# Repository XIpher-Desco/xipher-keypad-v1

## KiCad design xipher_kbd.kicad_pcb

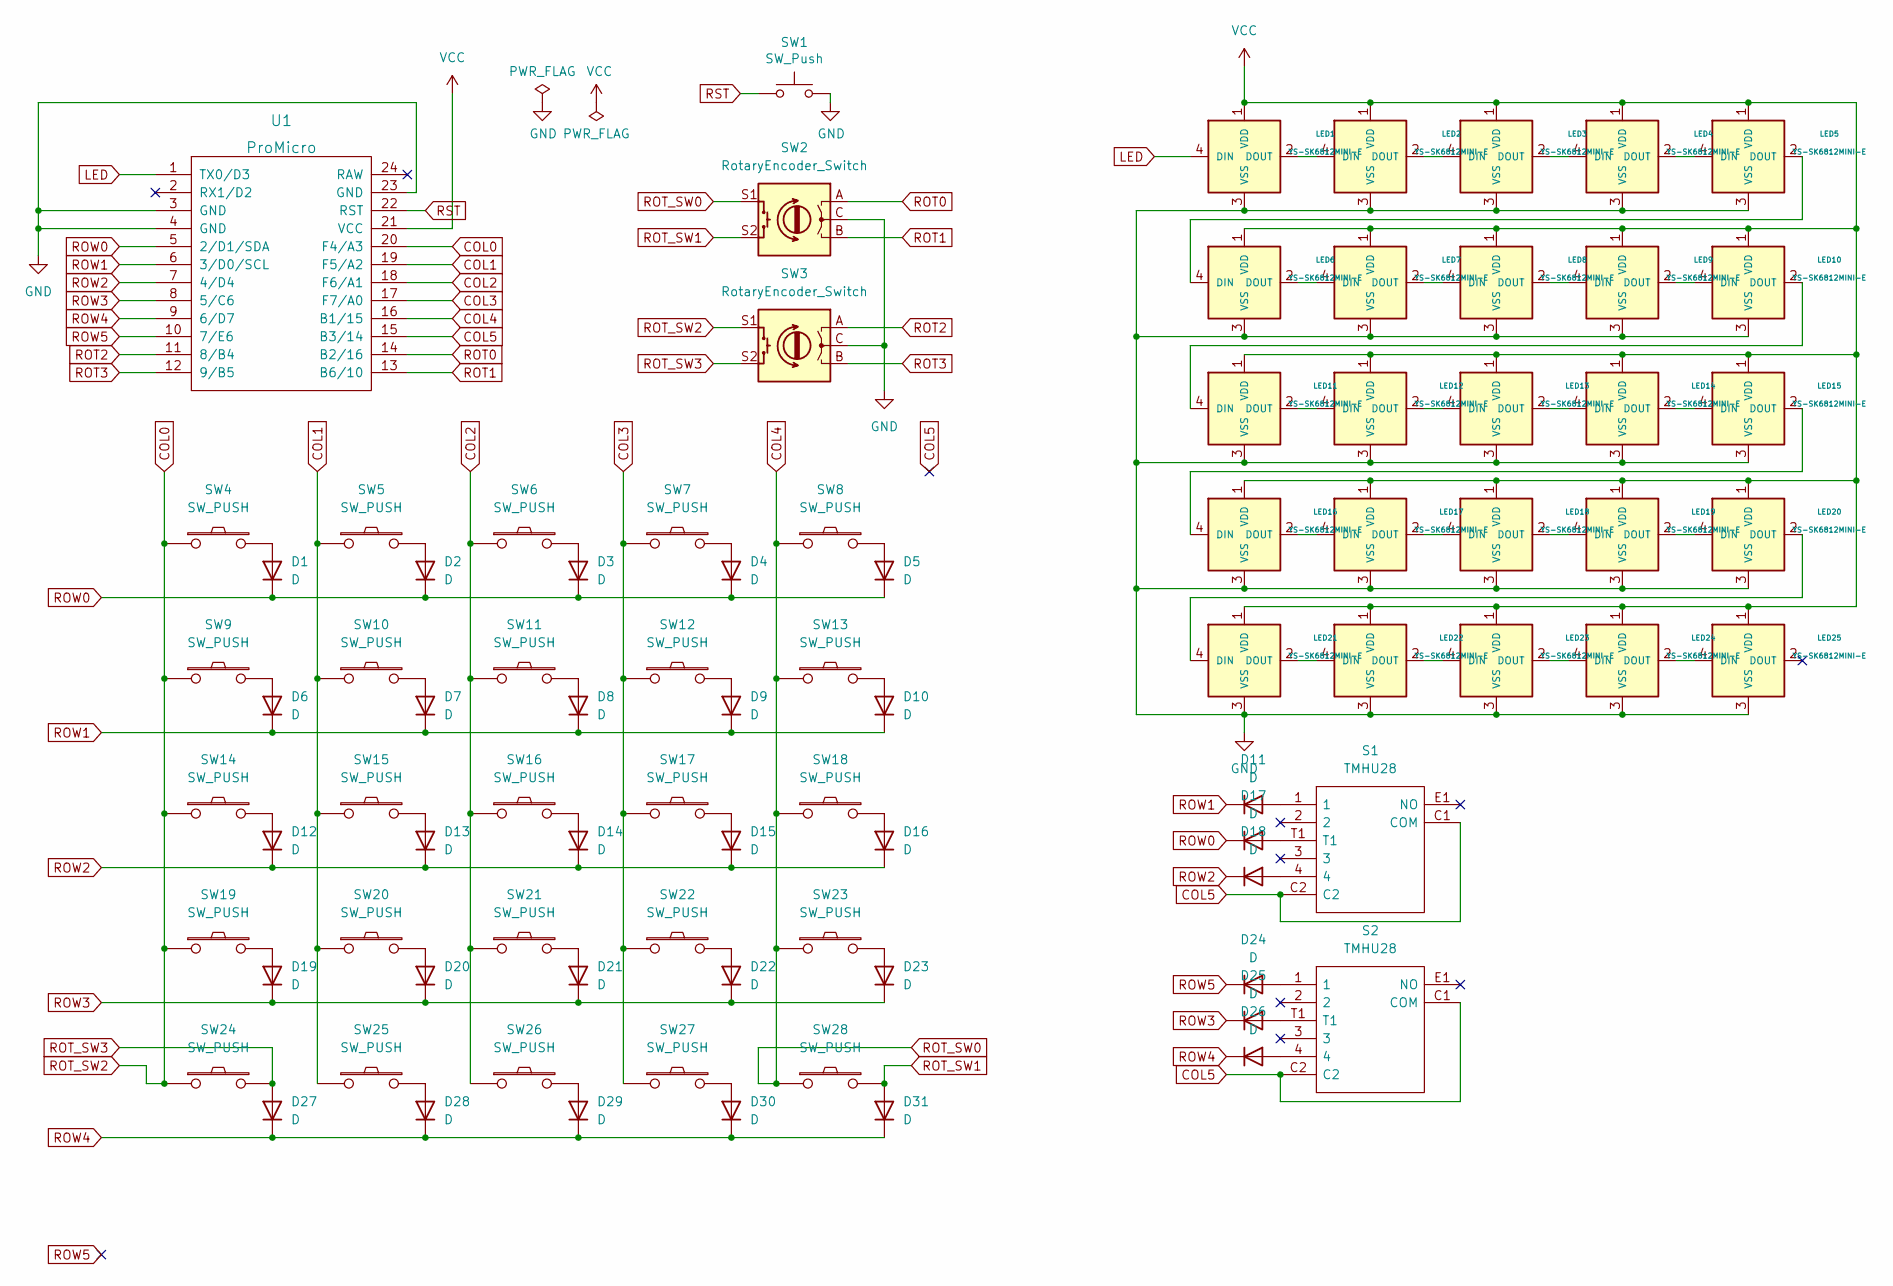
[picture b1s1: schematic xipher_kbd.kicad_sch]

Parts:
D1, D2, D3, D4, D5, D6, D7, D8, D9, D10, D11, D12, D13, D14, D15, D16, D17, D18, D19, D20, D21, D22, D23, D24, D25, D26, D27, D28, D29, D30, D31: D; D3_TH_SMD_v2
LED1, LED2, LED3, LED4, LED5, LED6, LED7, LED8, LED9, LED10, LED11, LED12, LED13, LED14, LED15, LED16, LED17, LED18, LED19, LED20, LED21, LED22, LED23, LED24, LED25: YS-SK6812MINI-E
S1, S2: TMHU28; Manufacturer_Part_Number TMHU28
SW1: SW_Push; ResetSW
SW2, SW3: RotaryEncoder_Switch; RotaryEncoder_Alps_EC11E-Switch_Vertical
SW4, SW5, SW6, SW7, SW8, SW9, SW10, SW11, SW12, SW13, SW14, SW15, SW16, SW17, SW18, SW19, SW20, SW21, SW22, SW23, SW26, SW27, SW28: SW_PUSH; CherryMX_Hotswap
SW24, SW25: SW_PUSH; CherryMX_1u
U1: ProMicro; ArduinoProMicro-ZigZag

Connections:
COL0: SW3.S1, SW4.1, SW9.1, SW14.1, SW19.1, SW24.1, U1.20 (F4/A3)
COL1: SW5.1, SW10.1, SW15.1, SW20.1, SW25.1, U1.19 (F5/A2)
COL2: SW6.1, SW11.1, SW16.1, SW21.1, SW26.1, U1.18 (F6/A1)
COL3: SW7.1, SW12.1, SW17.1, SW22.1, SW27.1, U1.17 (F7/A0)
COL4: SW2.S1, SW8.1, SW13.1, SW18.1, SW23.1, SW28.1, U1.16 (B1/15)
COL5: S1.C1 (COM), S1.C2, S2.C1 (COM), S2.C2, U1.15 (B3/14)
GND: LED1.3 (VSS), LED2.3 (VSS), LED3.3 (VSS), LED4.3 (VSS), LED5.3 (VSS), LED6.3 (VSS), LED7.3 (VSS), LED8.3 (VSS), LED9.3 (VSS), LED10.3 (VSS), LED11.3 (VSS), LED12.3 (VSS), LED13.3 (VSS), LED14.3 (VSS), LED15.3 (VSS), LED16.3 (VSS), LED17.3 (VSS), LED18.3 (VSS), LED19.3 (VSS), LED20.3 (VSS), LED21.3 (VSS), LED22.3 (VSS), LED23.3 (VSS), LED24.3 (VSS), LED25.3 (VSS), SW1.2, SW2.C, SW3.C, U1.3 (GND), U1.4 (GND), U1.23 (GND)
LED: LED1.4 (DIN), U1.1 (TX0/D3)
unnamed: D1.2 (A), SW4.2
unnamed: D2.2 (A), SW5.2
unnamed: D3.2 (A), SW6.2
unnamed: D4.2 (A), SW7.2
unnamed: D5.2 (A), SW8.2
unnamed: D6.2 (A), SW9.2
unnamed: D7.2 (A), SW10.2
unnamed: D8.2 (A), SW11.2
unnamed: D9.2 (A), SW12.2
unnamed: D10.2 (A), SW13.2
unnamed: D11.2 (A), S1.1
unnamed: D12.2 (A), SW14.2
unnamed: D13.2 (A), SW15.2
unnamed: D14.2 (A), SW16.2
unnamed: D15.2 (A), SW17.2
unnamed: D16.2 (A), SW18.2
unnamed: D17.2 (A), S1.T1
unnamed: D18.2 (A), S1.4
unnamed: D20.2 (A), SW20.2
unnamed: D21.2 (A), SW21.2
unnamed: D22.2 (A), SW22.2
unnamed: D24.2 (A), S2.1
unnamed: D25.2 (A), S2.T1
unnamed: D26.2 (A), S2.4
unnamed: D28.2 (A), SW25.2
unnamed: D29.2 (A), SW26.2
unnamed: D30.2 (A), SW27.2
unnamed: LED1.2 (DOUT), LED2.4 (DIN)
unnamed: LED2.2 (DOUT), LED3.4 (DIN)
unnamed: LED3.2 (DOUT), LED4.4 (DIN)
unnamed: LED4.2 (DOUT), LED5.4 (DIN)
unnamed: LED5.2 (DOUT), LED6.4 (DIN)
unnamed: LED6.2 (DOUT), LED7.4 (DIN)
unnamed: LED7.2 (DOUT), LED8.4 (DIN)
unnamed: LED8.2 (DOUT), LED9.4 (DIN)
unnamed: LED9.2 (DOUT), LED10.4 (DIN)
unnamed: LED10.2 (DOUT), LED11.4 (DIN)
unnamed: LED11.2 (DOUT), LED12.4 (DIN)
unnamed: LED13.2 (DOUT), LED14.4 (DIN)
unnamed: LED12.2 (DOUT), LED13.4 (DIN)
unnamed: LED15.2 (DOUT), LED16.4 (DIN)
unnamed: LED14.2 (DOUT), LED15.4 (DIN)
unnamed: LED16.2 (DOUT), LED17.4 (DIN)
unnamed: LED18.2 (DOUT), LED19.4 (DIN)
unnamed: LED17.2 (DOUT), LED18.4 (DIN)
unnamed: LED20.2 (DOUT), LED21.4 (DIN)
unnamed: LED19.2 (DOUT), LED20.4 (DIN)
unnamed: LED21.2 (DOUT), LED22.4 (DIN)
unnamed: LED23.2 (DOUT), LED24.4 (DIN)
unnamed: LED22.2 (DOUT), LED23.4 (DIN)
unnamed: LED24.2 (DOUT), LED25.4 (DIN)
ROT0: SW2.A, U1.14 (B2/16)
ROT1: SW2.B, U1.13 (B6/10)
ROT2: SW3.A, U1.11 (8/B4)
ROT3: SW3.B, U1.12 (9/B5)
ROW0: D1.1 (K), D2.1 (K), D3.1 (K), D4.1 (K), D5.1 (K), D17.1 (K), U1.5 (2/D1/SDA)
ROW1: D6.1 (K), D7.1 (K), D8.1 (K), D9.1 (K), D10.1 (K), D11.1 (K), U1.6 (3/D0/SCL)
ROW2: D12.1 (K), D13.1 (K), D14.1 (K), D15.1 (K), D16.1 (K), D18.1 (K), U1.7 (4/D4)
ROW3: D19.1 (K), D20.1 (K), D21.1 (K), D22.1 (K), D23.1 (K), D25.1 (K), U1.8 (5/C6)
ROW4: D26.1 (K), D27.1 (K), D28.1 (K), D29.1 (K), D30.1 (K), D31.1 (K), U1.9 (6/D7)
ROW5: D24.1 (K), U1.10 (7/E6)
RST: SW1.1, U1.22 (RST)
VCC: LED1.1 (VDD), LED2.1 (VDD), LED3.1 (VDD), LED4.1 (VDD), LED5.1 (VDD), LED6.1 (VDD), LED7.1 (VDD), LED8.1 (VDD), LED9.1 (VDD), LED10.1 (VDD), LED11.1 (VDD), LED12.1 (VDD), LED13.1 (VDD), LED14.1 (VDD), LED15.1 (VDD), LED16.1 (VDD), LED17.1 (VDD), LED18.1 (VDD), LED19.1 (VDD), LED20.1 (VDD), LED21.1 (VDD), LED22.1 (VDD), LED23.1 (VDD), LED24.1 (VDD), LED25.1 (VDD), U1.21 (VCC)

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
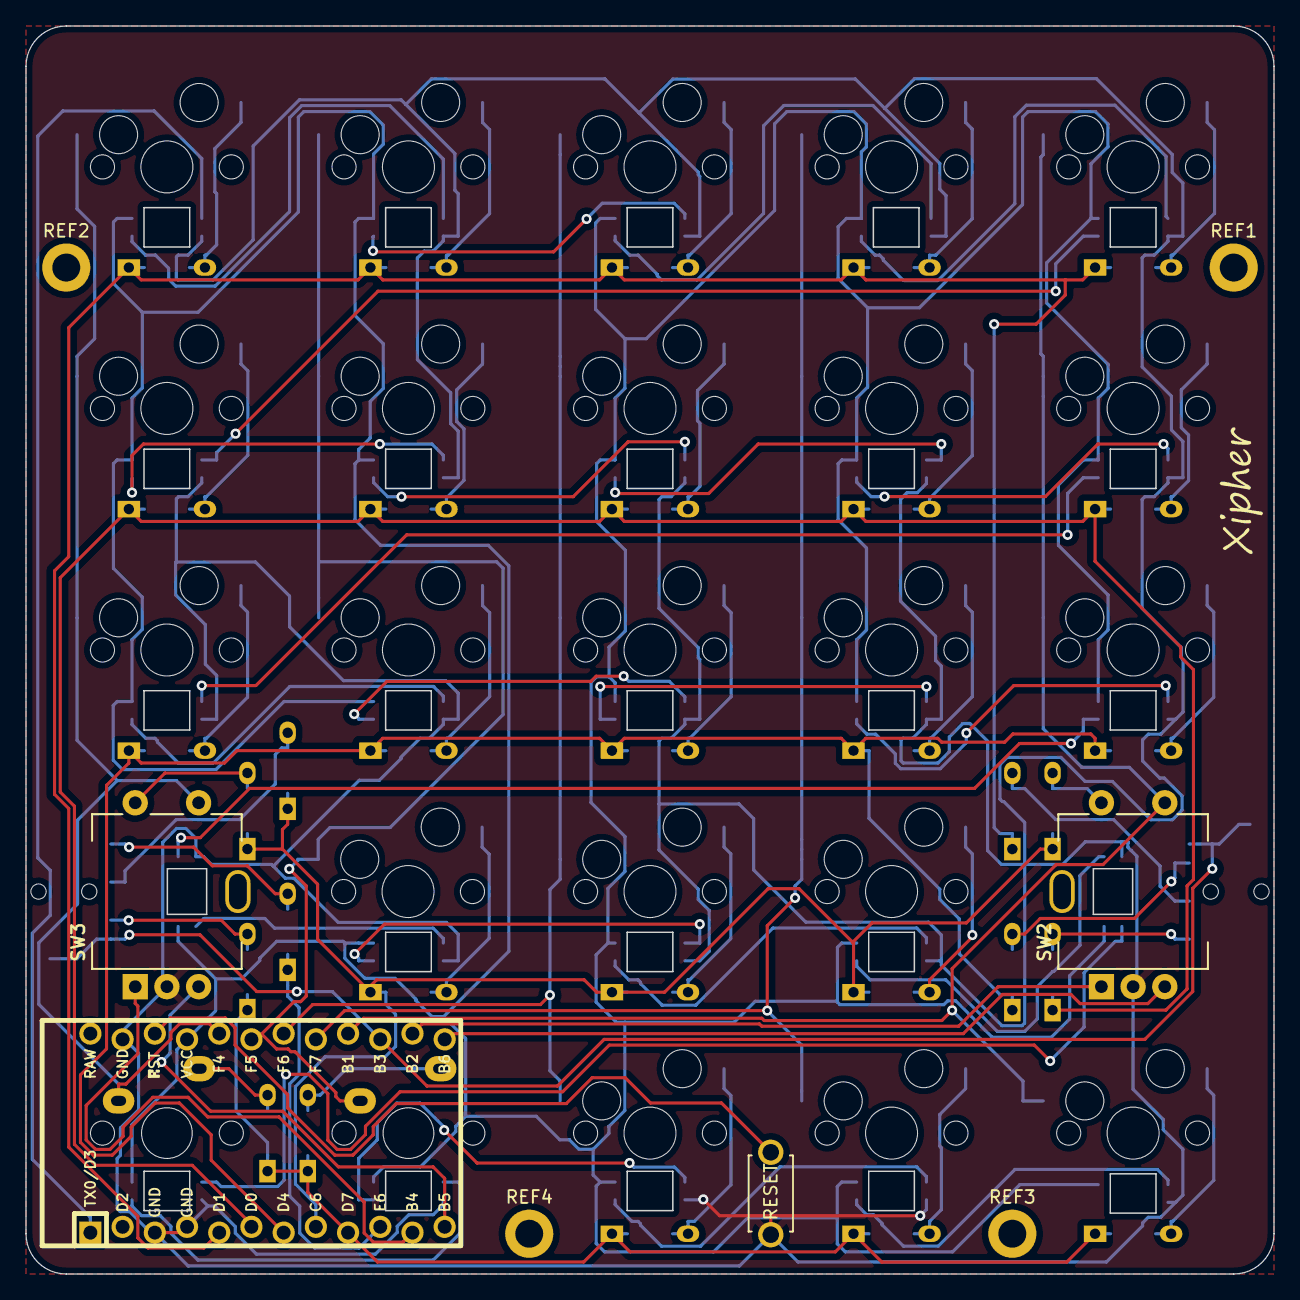
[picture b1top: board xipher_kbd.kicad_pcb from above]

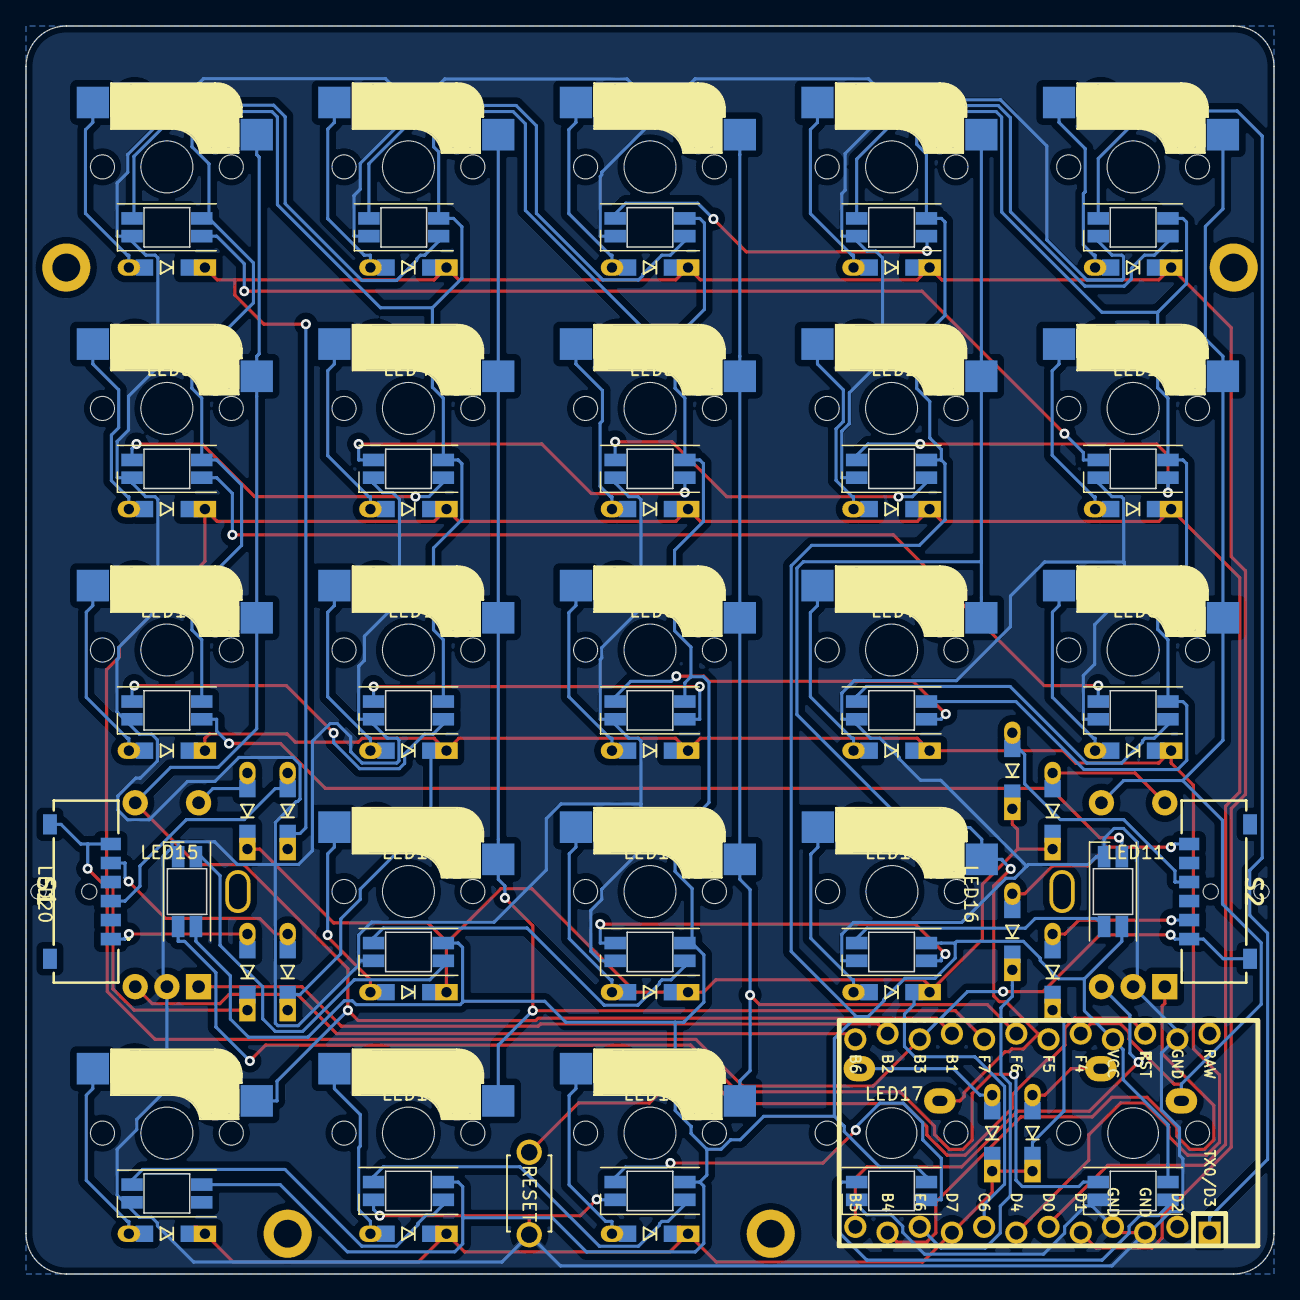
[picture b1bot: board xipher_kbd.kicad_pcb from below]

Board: 2 copper layers, 98.4 x 98.4 mm, 90 parts (59 on the bottom side), 75 nets.

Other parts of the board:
G1: LOGO; text_logo_10
REF1, REF2, REF3, REF4: MountingHole_2.2mm_M2_DIN965_Pad
